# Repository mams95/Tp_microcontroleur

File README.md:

# Tp_microcontroleur
Système à microcontrôleur
Bonjour le monde

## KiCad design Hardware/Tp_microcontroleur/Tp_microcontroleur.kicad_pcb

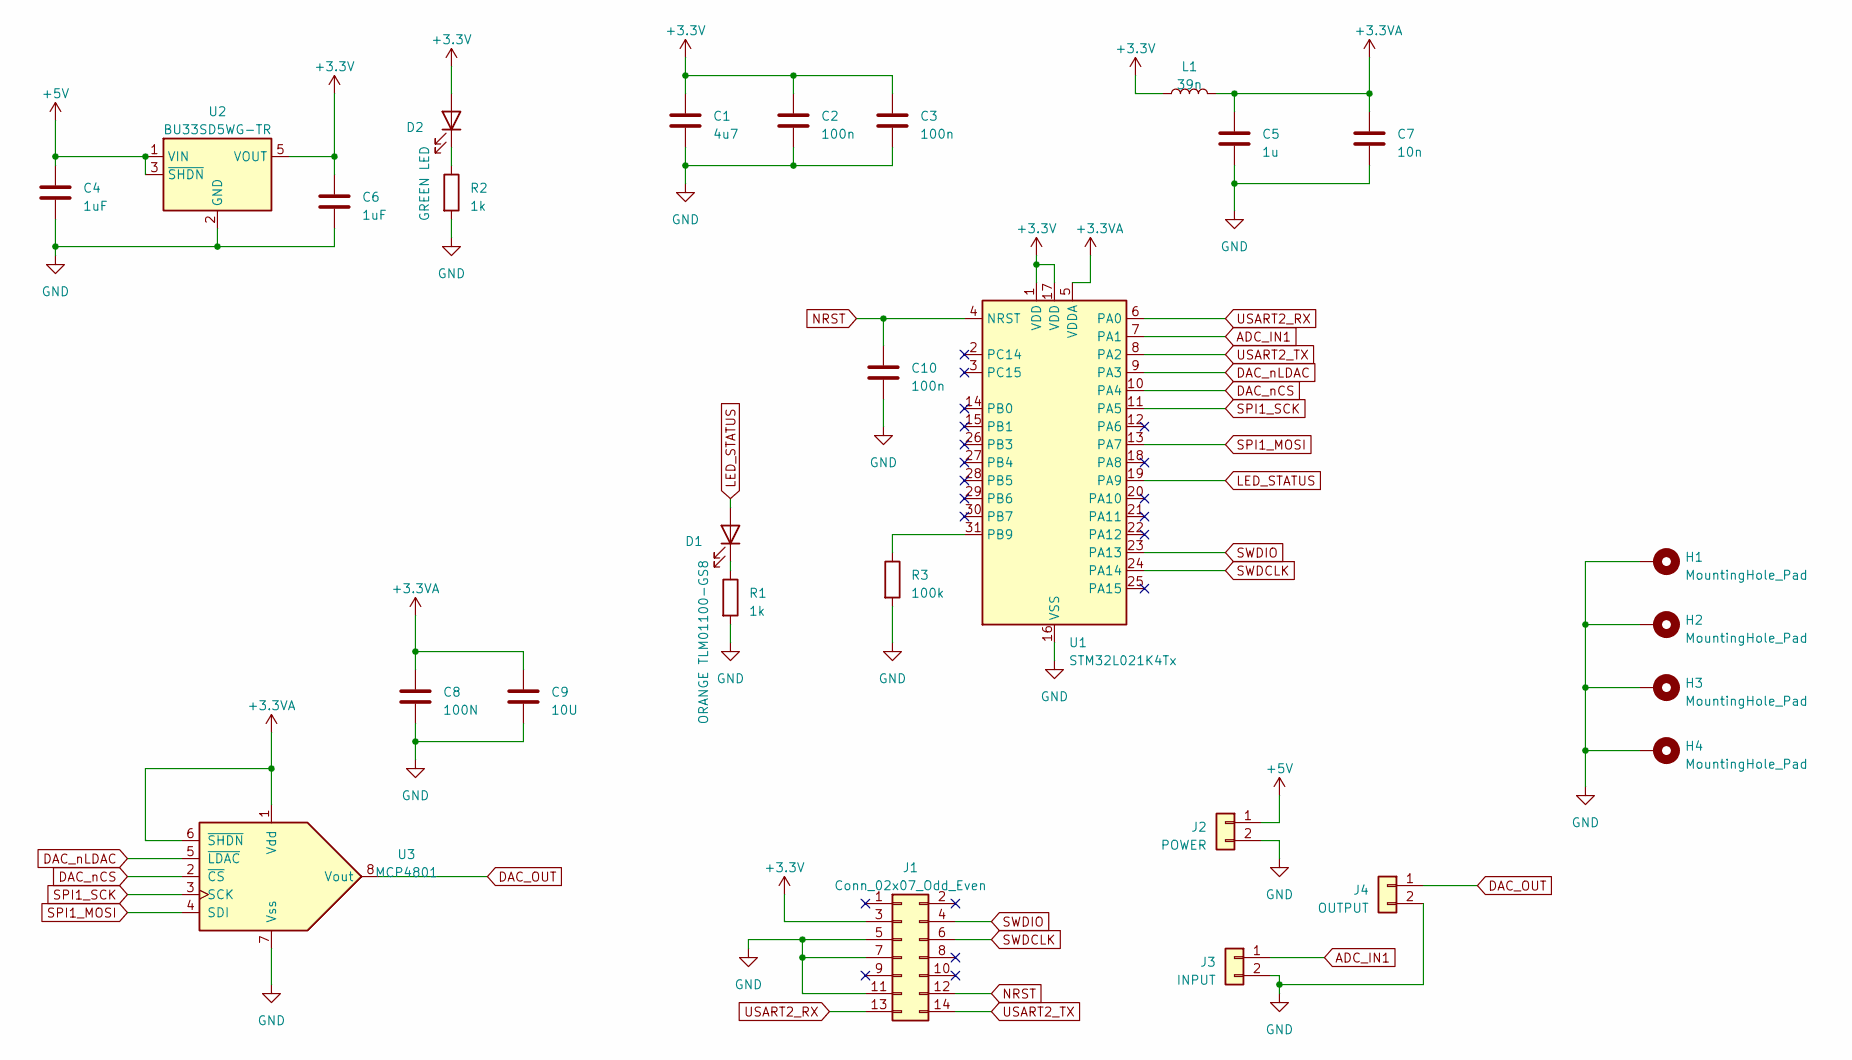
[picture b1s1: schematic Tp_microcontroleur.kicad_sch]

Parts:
C1: 4u7; C_0805_2012Metric_Pad1.18x1.45mm_HandSolder
C2, C3, C10: 100n; C_0805_2012Metric_Pad1.18x1.45mm_HandSolder
C4, C6: 1uF; C_0805_2012Metric_Pad1.18x1.45mm_HandSolder
C5: 1u; C_0805_2012Metric_Pad1.18x1.45mm_HandSolder
C7: 10n; C_0805_2012Metric_Pad1.18x1.45mm_HandSolder
C8: 100N; C_0805_2012Metric_Pad1.18x1.45mm_HandSolder
C9: 10U; C_0805_2012Metric_Pad1.18x1.45mm_HandSolder
D1: ORANGE TLM01100-GS8; LED_0603_1608Metric_Pad1.05x0.95mm_HandSolder
D2: GREEN LED; LED_0603_1608Metric_Pad1.05x0.95mm_HandSolder
H1, H2, H3, H4: MountingHole_Pad; MountingHole_3.2mm_M3_Pad
J1: Conn_02x07_Odd_Even; PinHeader_2x07_P1.27mm_Vertical_SMD
J2: POWER; JST_XH_B2B-XH-A_1x02_P2.50mm_Vertical
J3: INPUT; JST_XH_B2B-XH-A_1x02_P2.50mm_Vertical
J4: OUTPUT; JST_XH_B2B-XH-A_1x02_P2.50mm_Vertical
L1: 39n; L_0805_2012Metric_Pad1.05x1.20mm_HandSolder
R1, R2: 1k; R_0805_2012Metric_Pad1.20x1.40mm_HandSolder
R3: 100k; R_0805_2012Metric_Pad1.20x1.40mm_HandSolder
U1: STM32L021K4Tx; LQFP-32_7x7mm_P0.8mm
U2: BU33SD5WG-TR; SOT-23-5
U3: MCP4801; SOIC-8_3.9x4.9mm_P1.27mm

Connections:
+3.3V: C1.1, C2.1, C3.1, C6.1, D2.2 (A), J1.3, L1.1, U1.1 (VDD), U1.17 (VDD), U2.5 (VOUT)
+3.3VA: C5.1, C7.1, C8.1, C9.1, L1.2, U1.5 (VDDA), U3.1 (Vdd), U3.6 (~SHDN)
+5V: C4.1, J2.1, U2.1 (VIN), U2.3 (~SHDN)
ADC_IN1: J3.1, U1.7 (PA1)
DAC_OUT: J4.1, U3.8 (Vout)
DAC_nCS: U1.10 (PA4), U3.2 (~CS)
DAC_nLDAC: U1.9 (PA3), U3.5 (~LDAC)
GND: C1.2, C2.2, C3.2, C4.2, C5.2, C6.2, C7.2, C8.2, C9.2, C10.2, H1.1, H2.1, H3.1, H4.1, J1.5, J1.7, J1.11, J2.2, J3.2, J4.2, R1.2, R2.2, R3.2, U1.16 (VSS), U1.32 (VSS), U2.2 (GND), U3.7 (Vss)
LED_STATUS: D1.2 (A), U1.19 (PA9)
NRST: C10.1, J1.12, U1.4 (NRST)
unnamed: D1.1 (K), R1.1
unnamed: D2.1 (K), R2.1
unnamed: R3.1, U1.31 (PB9)
SPI1_MOSI: U1.13 (PA7), U3.4 (SDI)
SPI1_SCK: U1.11 (PA5), U3.3 (SCK)
SWDCLK: J1.6, U1.24 (PA14)
SWDIO: J1.4, U1.23 (PA13)
USART2_RX: J1.13, U1.6 (PA0)
USART2_TX: J1.14, U1.8 (PA2)

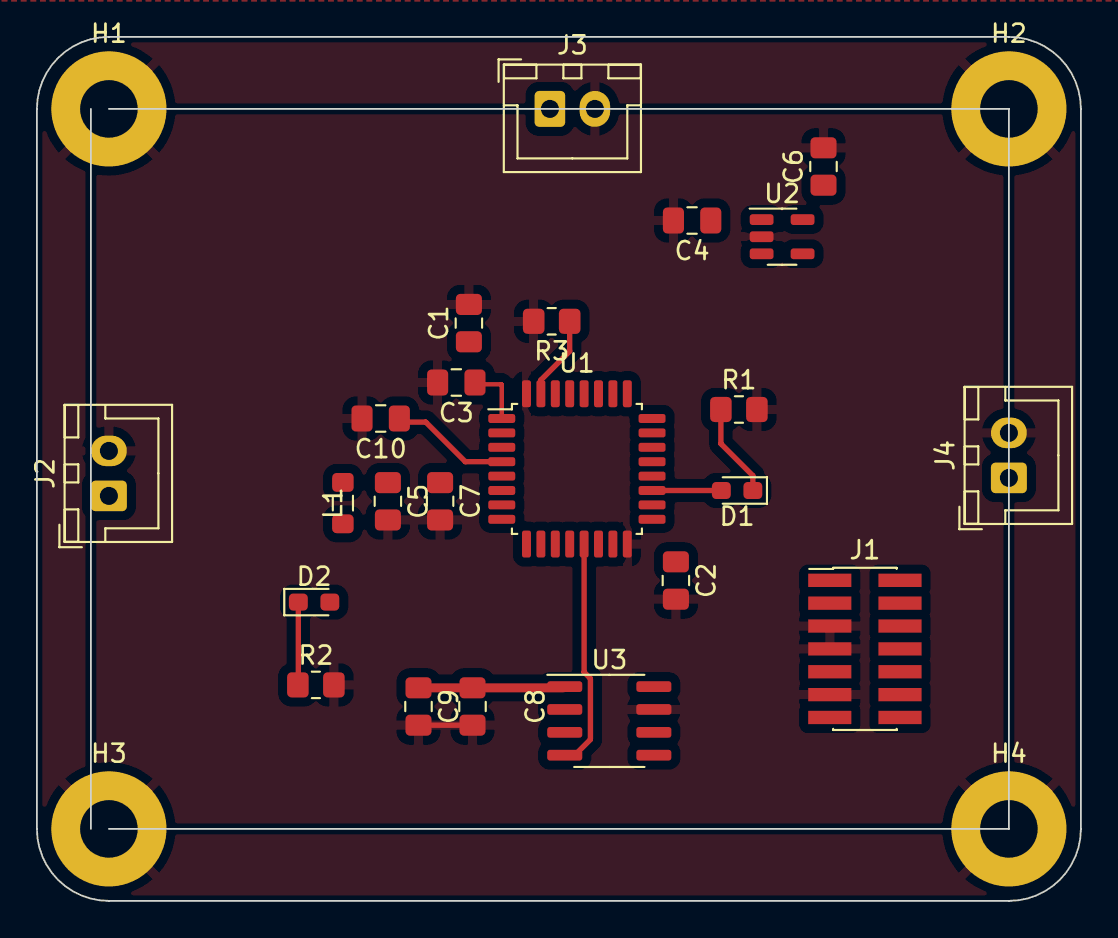
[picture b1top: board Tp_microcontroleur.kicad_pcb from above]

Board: 2 copper layers, 58.0 x 48.0 mm, 27 parts (0 on the bottom side), 19 nets.

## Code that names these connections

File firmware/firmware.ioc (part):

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Mcu.Name=STM32L021K4Tx
Mcu.Package=LQFP32
Mcu.UserName=STM32L021K4Tx
PA0-CK_IN.Mode=Asynchronous
PA0-CK_IN.Signal=USART2_RX
PA1.Mode=IN1
PA1.Signal=ADC_IN1
PA13.Mode=Serial_Wire
PA13.Signal=SYS_SWDIO
PA14.Mode=Serial_Wire
PA14.Signal=SYS_SWCLK
PA2.Mode=Asynchronous
PA2.Signal=USART2_TX
PA3.GPIOParameters=GPIO_Label
PA3.GPIO_Label=DAC_nLDAC
PA3.Signal=GPIO_Output
PA4.GPIOParameters=GPIO_Label
PA4.GPIO_Label=DAC_nCS
PA4.Signal=GPIO_Output
PA5.Mode=Full_Duplex_Master
PA5.Signal=SPI1_SCK
PA6.Mode=Full_Duplex_Master
PA6.Signal=SPI1_MISO
PA7.Mode=Full_Duplex_Master
PA7.Signal=SPI1_MOSI
PA8.Signal=S_TIM2_CH1
PA9.GPIOParameters=GPIO_Label
PA9.GPIO_Label=LED_STATUS
PA9.Signal=GPIO_Output
RCC.HSE_VALUE=8000000
RCC.SYSCLKFreq_VALUE=32000000
RCC.SYSCLKSource=RCC_SYSCLKSOURCE_PLLCLK
board=custom

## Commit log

2023-02-19 git add . git commit -m "First!"
